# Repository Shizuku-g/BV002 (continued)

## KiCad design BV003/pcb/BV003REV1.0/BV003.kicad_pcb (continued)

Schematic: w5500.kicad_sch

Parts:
C132: 0.1uF; C_0402_1005Metric; PARTNO GRM155R61A475MEAAD
C140: 100nf; C_0402_1005Metric; PARTNO GRM188R61E106KA73D
C145, C215: 10uF; C_0603_1608Metric; PARTNO CL10A106MO8NQNC; LCSC C92487 Hot
C206, C209, C210, C211, C212, C213: 0.1uF; C_0603_1608Metric; PARTNO CL10A106MO8NQNC; LCSC C92487 Hot
C207, C214, C216, C217: 10nf; C_0402_1005Metric; PARTNO GRM188R61E106KA73D
C208: 4.7uF; C_0402_1005Metric; PARTNO GRM155R61A475MEAAD
C218: 22nf; C_0402_1005Metric; PARTNO GRM188R61E106KA73D
FB9: D_0201_0603Metric
J7: RJ45_Hanrun_HR911105A_Horizontal
MISO1: TestPoint_Pad_D1.5mm
MOSI1: TestPoint_Pad_D1.5mm
R4: 1k; R_0402_1005Metric; PARTNO RC0402FR-071KL; LCSC C106235
R14: 10k; R_0402_1005Metric; PARTNO RC0402FR-071KL; LCSC C106235
R31: 10k; R_0402_1005Metric; PARTNO RC0402FR-072KL; LCSC C60488
R55: 12.4k; R_0402_1005Metric; PARTNO RC0402FR-072KL; LCSC C60488
R73, R104, R105, R126: 0R; R_0402_1005Metric; PARTNO RC0402FR-071KL; LCSC C106235
R127, R128, R129, R130: 49R9; R_0402_1005Metric; PARTNO RC0402FR-071KL; LCSC C106235
R131: 10R; R_0402_1005Metric; PARTNO RC0402FR-071KL; LCSC C106235
R132, R133: 0.33k; R_0402_1005Metric; PARTNO RC0402FR-071KL; LCSC C106235
RD+1: TestPoint_Pad_D1.5mm
RD-1: TestPoint_Pad_D1.5mm
SCLK1: TestPoint_Pad_D1.5mm
SCSN1: TestPoint_Pad_D1.5mm
TXN1: TestPoint_Pad_D1.5mm
TXP1: TestPoint_Pad_D1.5mm
U32: 25MHz; Oscillator_SMD_EuroQuartz_XO32-4Pin_3.2x2.5mm; PARTNO SX3M25.000E20F30THN
U33: W5500; LQFP-48_7x7mm_P0.5mm

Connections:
1V2_1: C207.2, U33.22 (1V2O); also elsewhere on the board
+3V3: C140.2, C145.1, FB9.2, J7.9, J7.12, R14.1, R31.2, R128.1, R129.1, R131.1, U32.1 (Standby), U32.4 (VDD); also elsewhere on the board
/T-Display-S3/MISO: MISO1.1, U33.34 (MISO); also elsewhere on the board
/T-Display-S3/MOSI: MOSI1.1, U33.35 (MOSI); also elsewhere on the board
/T-Display-S3/SCLK: SCLK1.1, U33.33 (SCLK); also elsewhere on the board
/T-Display-S3/SCSN: SCSN1.1, U33.32 (~SCS); also elsewhere on the board
/T-Display-S3/w5500/ACTLED: R133.2, U33.27 (ACTLED)
/T-Display-S3/w5500/LINKLED: R132.2, U33.25 (LINKLED)
AVDD: C206.1, C209.1, C210.1, C211.1, C212.1, C213.1, C215.1, FB9.1, U33.4 (AVDD), U33.8 (AVDD), U33.11 (AVDD), U33.15 (AVDD), U33.17 (AVDD), U33.21 (AVDD)
GND: C132.1, C206.2, C207.1, C208.1, C209.2, C210.2, C211.2, C212.2, C213.2, C214.1, C215.2, C218.1, J7.SH, R55.1, U32.2 (GND), U33.3 (AGND), U33.9 (AGND), U33.14 (AGND), U33.16 (AGND), U33.19 (AGND), U33.29 (GND), U33.43 (PMODE2), U33.44 (PMODE1), U33.45 (PMODE0), U33.48 (AGND); also elsewhere on the board
unnamed: C132.2, R4.1, R14.2
unnamed: C216.2, R126.2, R127.1
unnamed: C217.2, R105.2, R130.1
unnamed: J7.10, R133.1
unnamed: J7.11, R132.1
unnamed: C214.2, J7.5 (RCT), R127.2, R130.2
unnamed: C216.1, J7.3 (RD+), RD+1.1 (1_1)
unnamed: C217.1, J7.6 (RD-), RD-1.1 (1_1)
unnamed: C218.2, J7.4 (TCT), R131.2
unnamed: J7.1 (TD+), R104.2, R129.2, TXP1.1 (1_1)
unnamed: J7.2 (TD-), R73.2, R128.2, TXN1.1 (1_1)
unnamed: U32.3 (Out), U33.30 (XI/CLKIN)
unnamed: R55.2, U33.10 (EXRES1)
unnamed: R105.1, U33.5 (RXN)
unnamed: R126.1, U33.6 (RXP)
unnamed: C208.2, U33.20 (TOCAP)
unnamed: R73.1, U33.1 (TXN)
unnamed: R104.1, U33.2 (TXP)
unnamed: C140.1, C145.2, U33.28 (VDD)
unnamed: R31.1, U33.36 (~INT)
unnamed: R4.2, U33.37 (~RST)

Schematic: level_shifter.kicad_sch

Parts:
C98: 0.1uF; C_0402_1005Metric; PARTNO KGM05AR71C104KH
C99: 1uF; C_0402_1005Metric; PARTNO EMK105BJ105MV-F
R19, R22, R25, R28, R32, R33, R34, R35, R36: 1k; R_0402_1005Metric; PARTNO RC0402FR-071KL
R20, R21, R23, R24, R26, R27, R29, R30: 10k; R_0402_1005Metric; PARTNO RC0402JR-0710KL
U18: TLV3544; TSSOP-14_4.4x5mm_P0.65mm; PARTNO TLV3544IPWR

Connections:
+5V: C98.2, C99.2, U18.4 (V+); also elsewhere on the board
/BM1370/bm1373_3/BO: R27.1; also elsewhere on the board
/BM1370/bm1373_3/CO: R21.1; also elsewhere on the board
/BM1370/bm1373_3/RI: R36.1; also elsewhere on the board
/BM1370/bm1373_3/RSTO: R24.1; also elsewhere on the board
/BM1370/bm1373_4/level_shifter/BI2: R34.1, U18.8; also elsewhere on the board
/BM1370/bm1373_4/level_shifter/CI2: R32.1, U18.1; also elsewhere on the board
/BM1370/bm1373_4/level_shifter/NRSTI2: R33.1, U18.7; also elsewhere on the board
/BM1370/bm1373_4/level_shifter/RO2: R30.1; also elsewhere on the board
unnamed: R35.1, R36.2, U18.14
unnamed: R20.1, R21.2, U18.3 (+)
unnamed: R19.1, R32.2, U18.2 (-)
unnamed: R23.2, R24.2, U18.5 (+)
unnamed: R22.1, R33.2, U18.6 (-)
unnamed: R26.2, R27.2, U18.10 (+)
unnamed: R25.1, R34.2, U18.9 (-)
unnamed: R29.2, R30.2, U18.12 (+)
unnamed: R28.1, R35.2, U18.13 (-)
VDD: R20.2, R23.1, R26.1; also elsewhere on the board
VDD2: C98.1, C99.1, R29.1, U18.11 (V-); also elsewhere on the board
VDD3: R19.2, R22.2, R25.2, R28.2; also elsewhere on the board

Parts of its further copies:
C107, C109: 0.1uF; C_0402_1005Metric; PARTNO KGM05AR71C104KH
C108, C110: 1uF; C_0402_1005Metric; PARTNO EMK105BJ105MV-F
R43, R46, R49, R52, R56, R57, R58, R59, R60, R61, R64, R67, R70, R74, R75, R76, R77, R78: 1k; R_0402_1005Metric; PARTNO RC0402FR-071KL
R44, R45, R47, R48, R50, R51, R53, R54, R62, R63, R65, R66, R68, R69, R71, R72: 10k; R_0402_1005Metric; PARTNO RC0402JR-0710KL
U25, U26: TLV3544; TSSOP-14_4.4x5mm_P0.65mm; PARTNO TLV3544IPWR

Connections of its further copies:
+5V: C107.2, C108.2, C109.2, C110.2, U25.4 (V+), U26.4 (V+); also elsewhere on the board
/BM1370/bm1373_1/BO: R51.1; also elsewhere on the board
/BM1370/bm1373_1/CO: R45.1; also elsewhere on the board
/BM1370/bm1373_1/RI: R60.1; also elsewhere on the board
/BM1370/bm1373_1/RSTO: R48.1; also elsewhere on the board
/BM1370/bm1373_2/BO: R69.1; also elsewhere on the board
/BM1370/bm1373_2/CO: R63.1; also elsewhere on the board
/BM1370/bm1373_2/RI: R78.1; also elsewhere on the board
/BM1370/bm1373_2/RSTO: R66.1; also elsewhere on the board
/BM1370/bm1373_2/level_shifter/BI2: R58.1, U25.8; also elsewhere on the board
/BM1370/bm1373_2/level_shifter/CI2: R56.1, U25.1; also elsewhere on the board
/BM1370/bm1373_2/level_shifter/NRSTI2: R57.1, U25.7; also elsewhere on the board
/BM1370/bm1373_2/level_shifter/RO2: R54.1; also elsewhere on the board
/BM1370/bm1373_3/level_shifter/BI2: R76.1, U26.8; also elsewhere on the board
/BM1370/bm1373_3/level_shifter/CI2: R74.1, U26.1; also elsewhere on the board
/BM1370/bm1373_3/level_shifter/NRSTI2: R75.1, U26.7; also elsewhere on the board
/BM1370/bm1373_3/level_shifter/RO2: R72.1; also elsewhere on the board
GND: C107.1, C108.1, R53.1, U25.11 (V-); also elsewhere on the board
unnamed: R59.1, R60.2, U25.14
unnamed: R77.1, R78.2, U26.14
unnamed: R44.1, R45.2, U25.3 (+)
unnamed: R43.1, R56.2, U25.2 (-)
unnamed: R47.2, R48.2, U25.5 (+)
unnamed: R46.1, R57.2, U25.6 (-)
unnamed: R50.2, R51.2, U25.10 (+)
unnamed: R49.1, R58.2, U25.9 (-)
unnamed: R53.2, R54.2, U25.12 (+)
unnamed: R52.1, R59.2, U25.13 (-)
unnamed: R62.1, R63.2, U26.3 (+)
unnamed: R61.1, R74.2, U26.2 (-)
unnamed: R65.2, R66.2, U26.5 (+)
unnamed: R64.1, R75.2, U26.6 (-)
unnamed: R68.2, R69.2, U26.10 (+)
unnamed: R67.1, R76.2, U26.9 (-)
unnamed: R71.2, R72.2, U26.12 (+)
unnamed: R70.1, R77.2, U26.13 (-)
VDD1: C109.1, C110.1, R43.2, R46.2, R49.2, R52.2, R71.1, U26.11 (V-); also elsewhere on the board
VDD2: R44.2, R47.1, R50.1, R61.2, R64.2, R67.2, R70.2; also elsewhere on the board
VDD3: R62.2, R65.1, R68.1; also elsewhere on the board

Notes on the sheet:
OPAMP Bypass

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
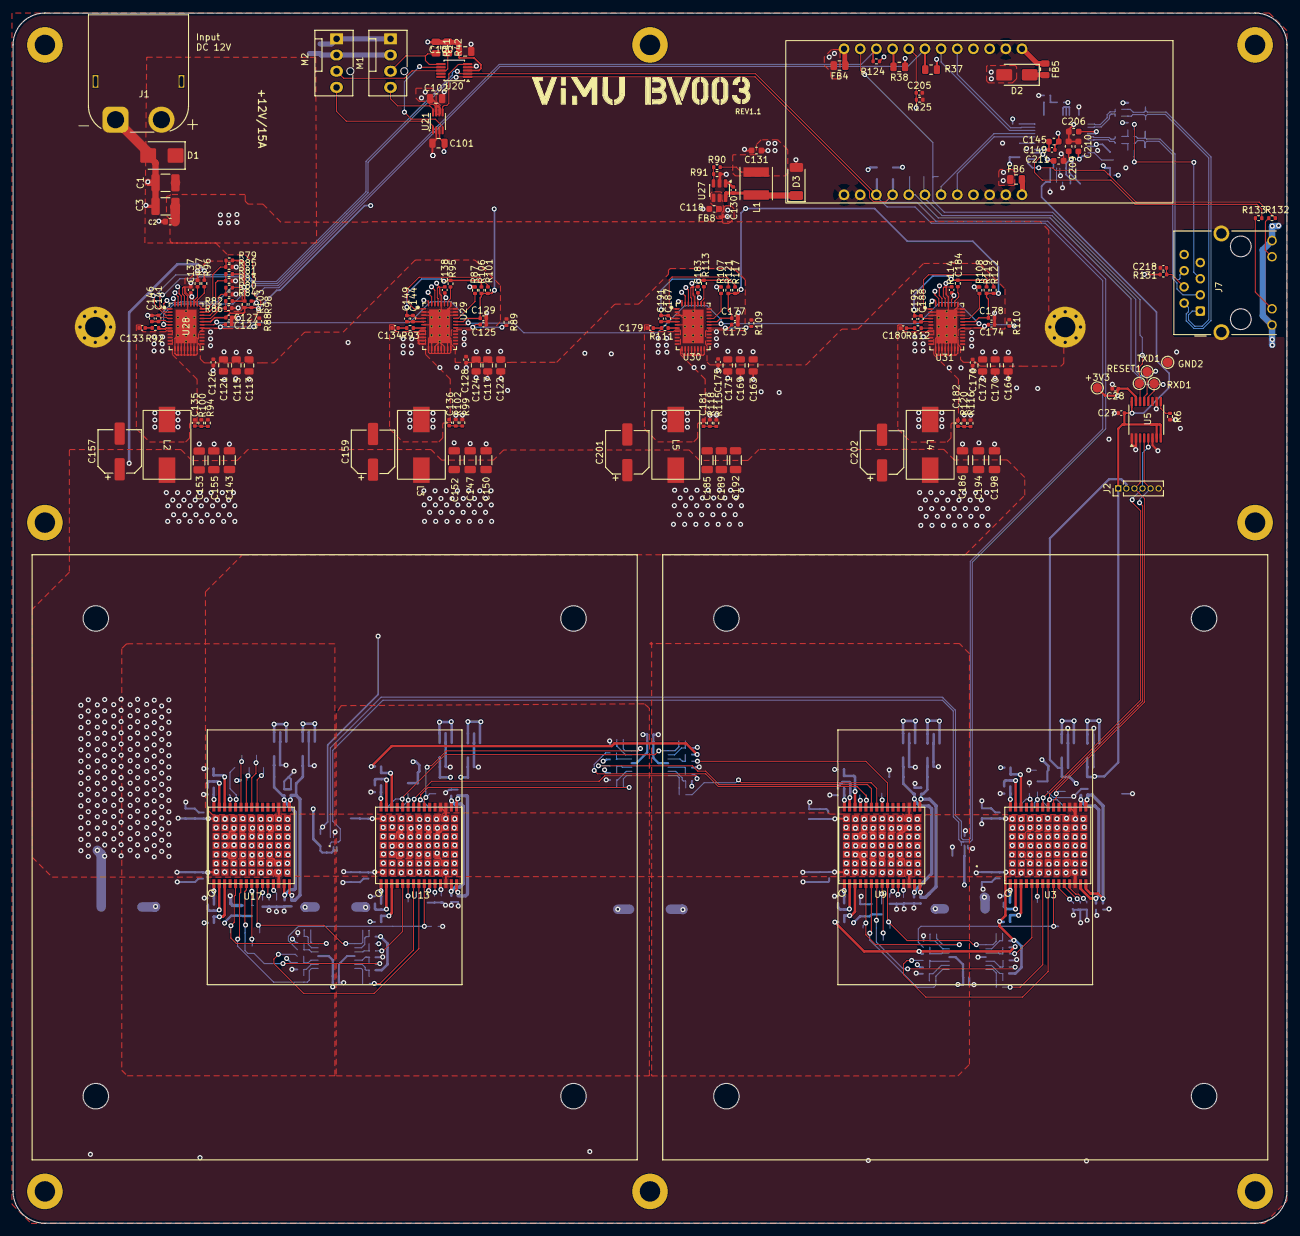
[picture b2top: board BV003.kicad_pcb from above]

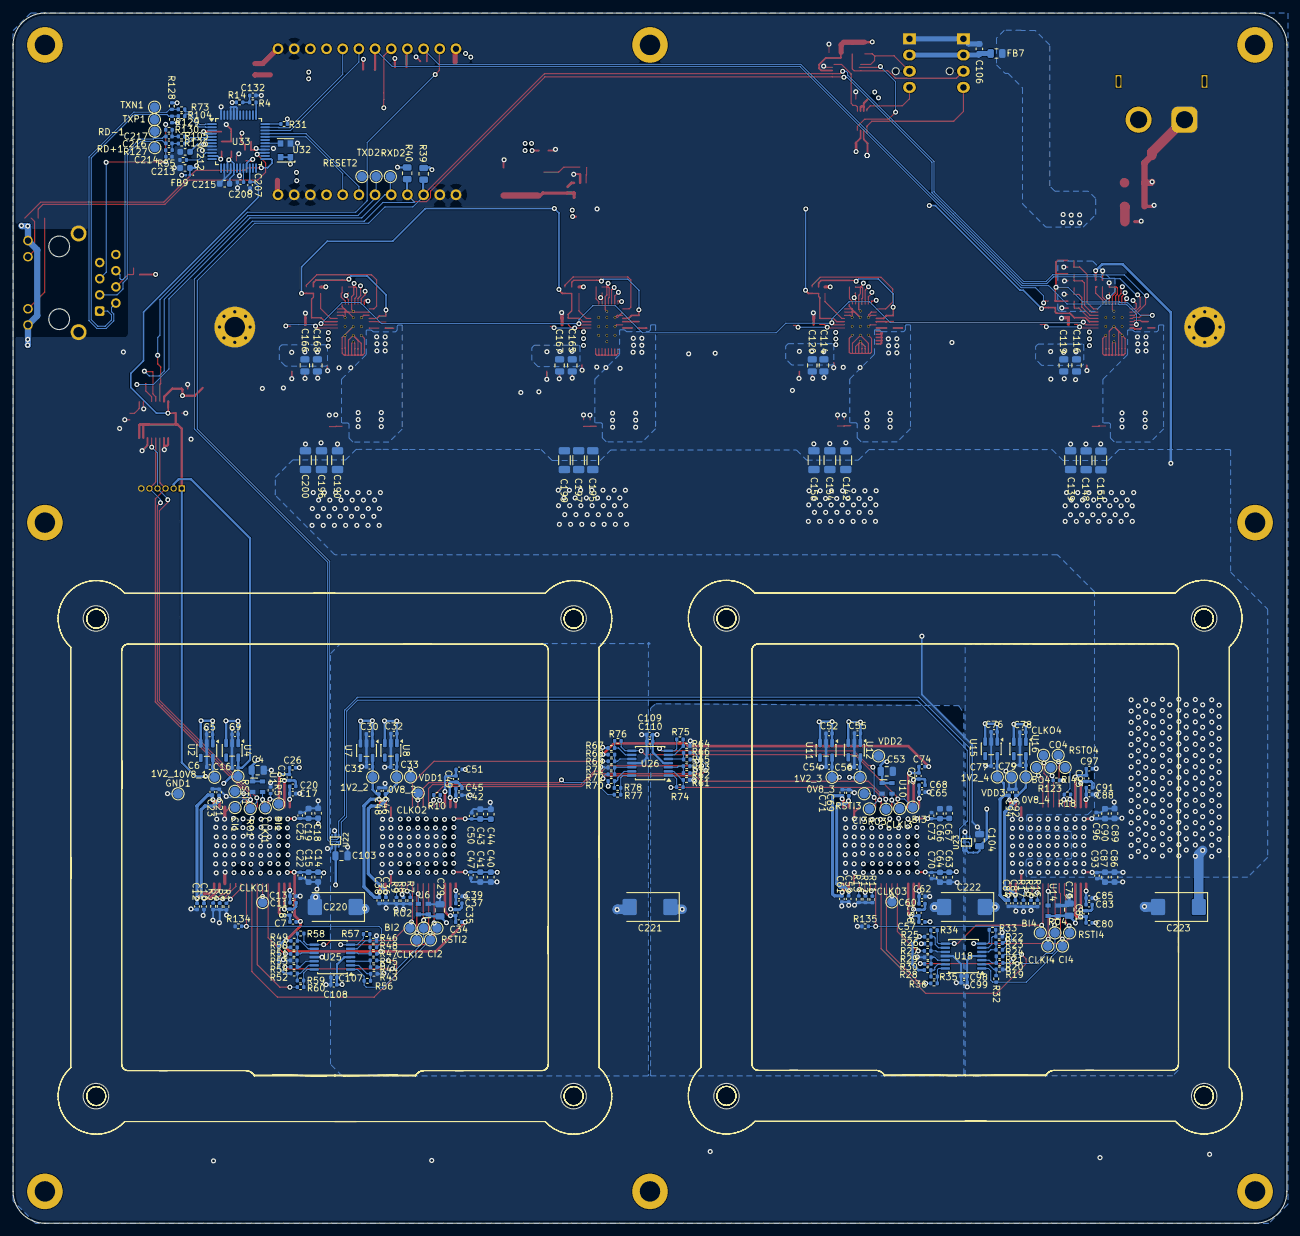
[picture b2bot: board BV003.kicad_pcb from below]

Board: 4 copper layers, 200.0 x 190.0 mm, 457 parts (285 on the bottom side), 224 nets.

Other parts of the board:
C220, C221, C222, C223: 330uf; CP_EIA-7343-31_Kemet-D_Pad2.25x2.55mm_HandSolder
CLKO1, CLKO2, CLKO3: TestPoint_Pad_D1.5mm
GND2: TestPoint_Pad_D1.5mm
H1, H2: MountingHole_Pad; MountingHole_3.2mm_M3_Pad_Via
R134, R135: 10k; R_0402_1005Metric

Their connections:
/BM1370/bm1373_1/RSTO: R134.2; also elsewhere on the board
/BM1370/bm1373_3/RSTO: R135.2; also elsewhere on the board
GND: C220.2, GND2.1 (1_1), H1.1 (1_1), H2.1 (1_1), R134.1; also elsewhere on the board
unnamed 110: CLKO1.1 (1_1); also elsewhere on the board
unnamed 121: CLKO2.1 (1_1); also elsewhere on the board
unnamed 131: CLKO3.1 (1_1); also elsewhere on the board
VDD: C223.1; also elsewhere on the board
VDD1: C220.1, C221.2; also elsewhere on the board
VDD2: C221.1, C222.2, R135.1; also elsewhere on the board
VDD3: C222.1, C223.2; also elsewhere on the board

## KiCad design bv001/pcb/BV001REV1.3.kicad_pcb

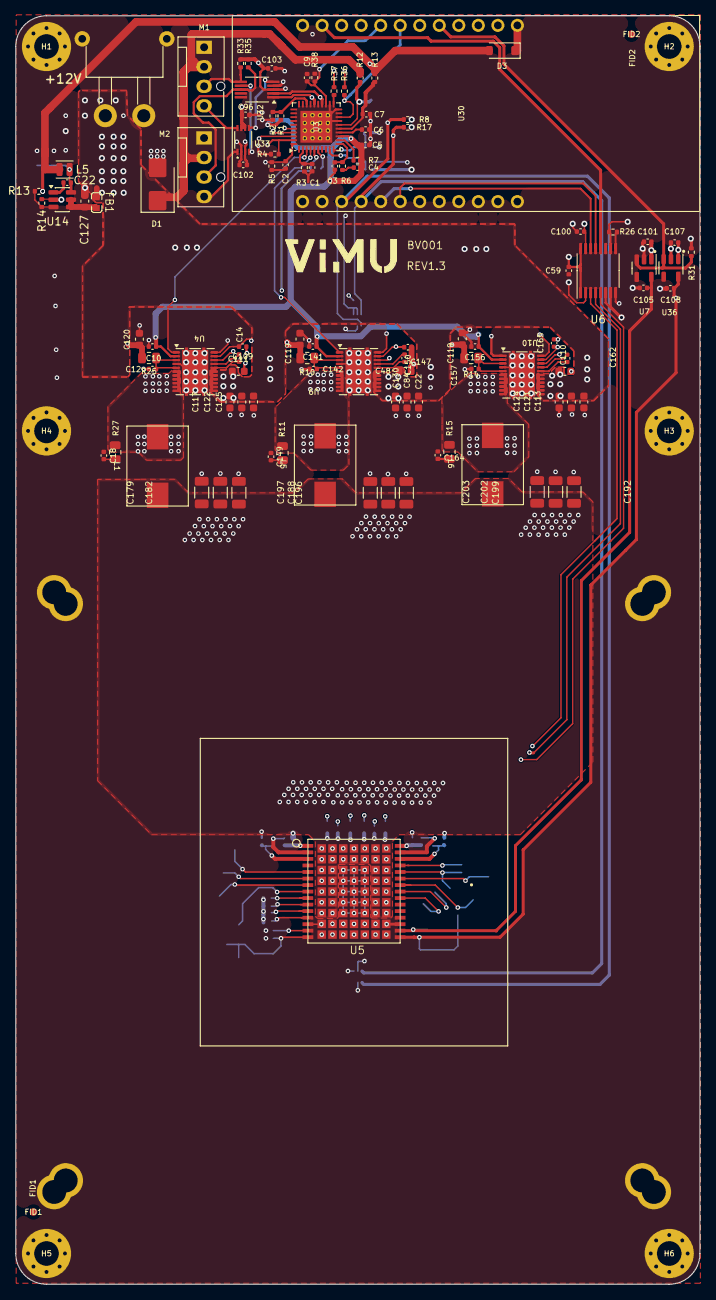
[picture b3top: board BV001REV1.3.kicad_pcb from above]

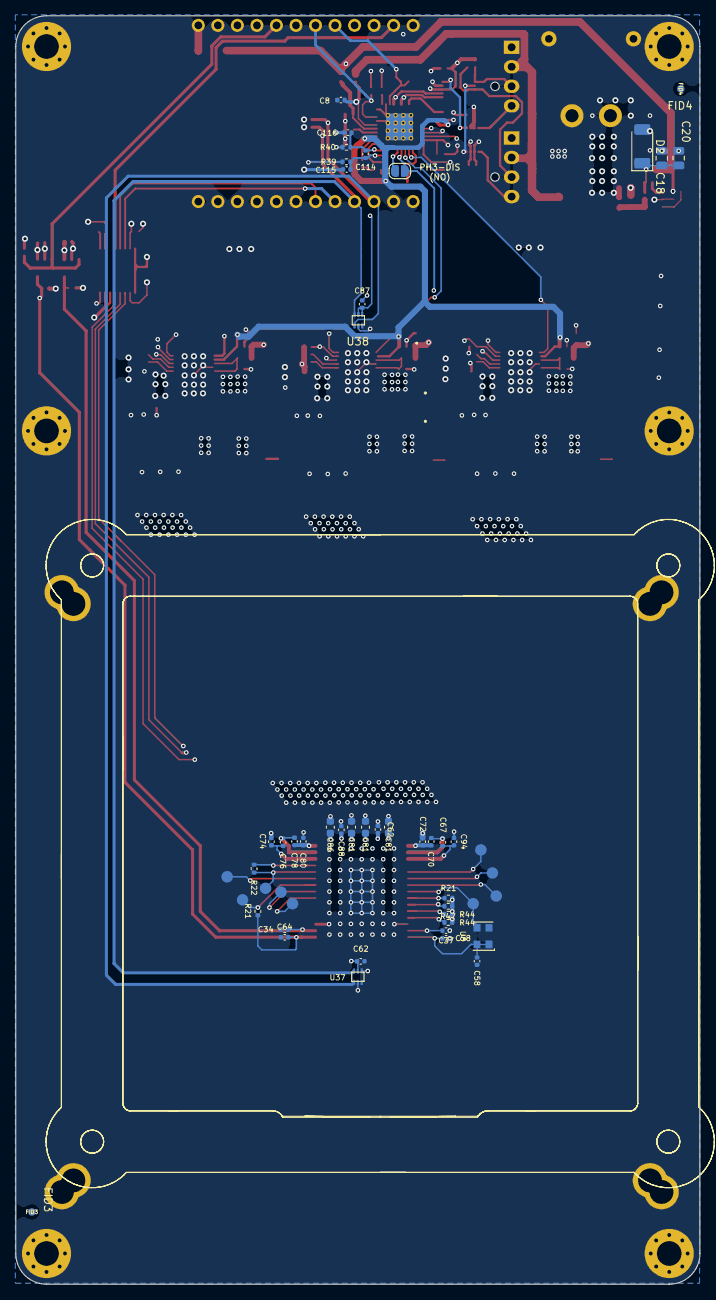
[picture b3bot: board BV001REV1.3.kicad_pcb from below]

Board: 6 copper layers, 89.0 x 165.0 mm, 156 parts (42 on the bottom side), 79 nets.

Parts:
C1: 2.2nF; C_0402_1005Metric
C2, C4, C9, C18, C109, C149, C150, C164, C165: 1nF; C_0402_1005Metric
C3: 12pF; C_0402_1005Metric
C5: 330nF; C_0402_1005Metric
C6, C8, C34, C37, C58, C58#2, C64, C67, C70, C72, C74, C76, C78, C80, C94, C105, C108: 1µF; C_0402_1005Metric
C7: 4.7µF; C_0402_1005Metric
C10, C14, C87, C96, C101, C102, C103, C107, C141, C147, C156, C162: 100nF; C_0402_1005Metric
C12, C142, C157: 2.2µF; C_0402_1005Metric
C18#2, C20: 10uF; C_0805_2012Metric
C22, C48, C81, C81#2, C81#3, C84, C86, C110, C111, C113, C117, C121, C122, C124, C125, C127, C130: 10uF; C_0603_1608Metric
C22#2: 10nf; C_0402_1005Metric
C59, C100: 0.1uF; C_0402_1005Metric
C62: 100pF; C_0402_1005Metric
C62#2: 100nf; C_0402_1005Metric
C88: 33pf; C_0402_1005Metric
C114, C115, C116: 22pF; C_0402_1005Metric
C119, C119#2, C120: 10µF; C_0603_1608Metric
C179, C182, C188, C192, C196, C197, C199, C202, C203: 100µF; C_1206_3216Metric
D1: 5KPxxA; D_SMB
D2: D_SOD-128
D3: 1N5819; D_SOD-123
FB1: FB0603
FID1, FID2, FID3, FID4: Fiducial_1mm_Mask2mm
H1, H2, H3, H4, H5, H6: MountingHole_Pad; MountingHole_3.2mm_M3_Pad_Via
J1: XT30; XT30PW-M
JP3: SolderJumper_2_Open; SolderJumper-2_P1.3mm_Open_RoundedPad1.0x1.5mm
L1, L5#2, L6: 220nH; IFLR-4031GC-01-8x10
L5: 4.7uH; L_Changjiang_FTC201612S
M1, M2: Fan_4pin; FanPinHeader_1x04_P2.54mm_Vertical
R1: 16.5k; R_0402_1005Metric
R2: 24.3k; R_0402_1005Metric
R3: 66.5k; R_0402_1005Metric
R4: 100k; R_0402_1005Metric
R5: 121k; R_0402_1005Metric
R6: 8.06k; R_0402_1005Metric
R7: 2.55k; R_0402_1005Metric
R8, R17: 4.7k; R_0402_1005Metric
R10, R11, R14, R15, R25, R27: 1R/0.5w; R_0805_2012Metric
R12, R13: 2.2R; R_0402_1005Metric
R13#2: 84.5k; R_0402_1005Metric
R14#2: 16.2k; R_0402_1005Metric
R21, R21#2, R22, R31, R36, R37, R38: 10k; R_0402_1005Metric
R26: 20k; R_0402_1005Metric
R33, R35: 2.7k; R_0402_1005Metric
R39, R40: 100R; R_0402_1005Metric
R44, R44#2, R47: 1k; R_0402_1005Metric
U3: TPS53647; Texas_RHA0040B_VQFN-40-1EP_6x6mm_P0.5mm_EP4.15x4.15mm_Therm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
U4, U9, U10: CSD95472Q5MC; CSD95472-SON-5x6
U5: B1373CC
U6: SN74AVC4T774; TSSOP-16_4.4x5mm_P0.65mm
U7: MCP1824T-0802E; SOT-23-5
U8: 25MHz; Oscillator_SMD_EuroQuartz_XO32-4Pin_3.2x2.5mm
U14: SOT-23-6
U30: T-Display-S3
U32: EMC2302-1; MSOP-10_3x3mm_P0.5mm
U33: TXU0102-DCU; VSSOP-8_2.3x2mm_P0.5mm
U36: MCP1824T-1202E; SOT-23-5
U37, U38: TMP1075; TMP1075-DRL

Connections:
+0V8: C34.2, C37.2, C105.1, U5.14 (VDDIO_08_0), U5.17 (VDDIO_08_1), U7.5 (VOUT)
+1V2: C58.1, C58#2.1, C59.1, C64.1, C108.1, R21.2, U5.15 (VDDIO_12_0), U5.16 (VDDIO_12_1), U6.1 (DIR1), U6.8 (DIR4), U6.16 (VCCA), U8.1 (Standby), U8.4 (VDD), U36.5 (VOUT)
+3V3: C62#2.2, C87.1, C100.1, C101.1, C102.1, C103.1, C107.1, JP3.2 (B), R8.2, R17.2, R33.1, R35.1, R36.1, R37.1, U3.6 (CSP4), U6.15 (VCCB), U7.1 (VIN), U30.1 (3V), U30.13 (3V), U32.3 (VDD), U33.3 (VCCA), U36.1 (VIN), U37.5 (V+), U38.4 (A0), U38.5 (V+)
+5V: C96.1, C119.1, C119#2.1, C120.1, D3.2 (A), L5.2, R10.1, R13.1, R13#2.2, R14.1, R25.1, U33.6 (OE), U33.7 (VCCB)
+12V: C22.1, C48.1, C84.1, C110.1, C111.1, C113.1, C117.1, C121.1, C122.1, C124.1, C125.1, C130.1, D1.1 (A1), FB1.1, J1.1 (+V), M1.2 (+), M2.2 (+), R12.1, U4.7 (VIN), U9.7 (VIN), U10.7 (VIN)
+VRef: C3.2, C4.2, C5.1, C10.1, C141.1, C156.1, R1.2, R7.1, U3.13 (VREF), U4.2 (REFIN), U9.2 (REFIN), U10.2 (REFIN)
/BM1366/BI: R21#2.2, U5.9 (BI)
/BM1366/RESET: U6.12 (B3), U30.2 (GPIO1)
/BM1366/RXD: U6.14 (B1), U30.20 (GPIO18)
/BM1366/TXD: U6.13 (B2), U30.19 (GPIO17)
/Power/FCCM: R4.2, U3.39 (/SKIP-NVM), U4.10 (FCCM), U9.10 (FCCM), U10.10 (FCCM)
/Power/LDO_EN: R31.1, U7.3 (EN), U30.8 (GPIO13), U36.3 (EN)
/Power/PWR_EN: C9.1, R38.1, U3.23 (ENABLE), U30.5 (GPIO10)
/Power/TPS_CSP1: U3.3 (CSP1), U4.1 (IOUT)
/Power/TPS_CSP2: U3.4 (CSP2), U9.1 (IOUT)
/Power/TPS_CSP3: JP3.1 (A), U3.5 (CSP3), U10.1 (IOUT)
/Power/TPS_PWM1: U3.38 (PWM1), U4.12 (PWM)
/Power/TPS_PWM2: U3.37 (PMW2), U9.12 (PWM)
/Power/TPS_PWM3: U3.36 (PMW3), U10.12 (PWM)
/Power/TPS_TSEN: C2.1, C109.1, C150.1, C165.1, R5.2, U3.40 (TSEN), U4.11 (TAO/FAULT), U9.11 (TAO/FAULT), U10.11 (TAO/FAULT)
/Power/VR_RDY: R36.2, U3.18 (VR_RDY), U30.6 (GPIO11)
/Power//RESET: R37.2, U3.21 (/RESET)
/T-Display-S3/SCL: R8.1, U3.24 (PMB_CLK), U30.22 (GPIO43), U32.2 (SCL), U37.1 (SCL), U38.1 (SCL)
/T-Display-S3/SDA: R17.1, U3.26 (PMB_DIO), U30.21 (GPIO44), U32.1 (SDA), U37.6 (SDA), U38.6 (SDA)
/T-Display-S3/TACHO1: M1.3 (Tacho), R33.2, U32.6 (TACH1)
/T-Display-S3/TACHO2: M2.3 (Tacho), R35.2, U32.8 (TACH2)
CI-N: U5.6 (CI), U6.4 (A2)
CLK-N: U5.8 (CLKI), U8.3 (Out)
GND: C1.2, C2.2, C5.2, C6.2, C7.1, C8.1, C9.2, C10.2, C12.2, C18.2, C18#2.2, C20.2, C22.2, C34.1, C37.1, C48.2, C58.2, C58#2.2, C59.2, C62.2, C62#2.1, C64.2, C72.2, C80.2, C81.2, C81#2.2, C81#3.2, C84.2, C86.2, C87.2, C88.2, C96.2, C100.2, C101.2, C102.2, C103.2, C105.2, C107.2, C108.2, C109.2, C110.2, C111.2, C113.2, C115.1, C116.2, C117.2, C119.2, C119#2.2, C120.2, C121.2, C122.2, C124.2, C125.2, C127.2, C130.2, C141.2, C142.2, C149.2, C150.2, C156.2, C157.2, C164.2, C165.2, C179.2, C182.2, C188.2, C192.2, C196.2, C197.2, C199.2, C202.2, C203.2, D1.2 (A2), D2.2, H1.1, H2.1, H3.1, H4.1, H5.1, H6.1, J1.2 (GND), M1.1 (-), M2.1 (-), R2.1, R3.1, R4.1, R5.1, R14#2.1, R21#2.1, R26.1, R31.2, R38.2, R40.1, R44.2, R44#2.2, R47.2, U3.17 (GND), U3.20 (GND), U3.22 (GND), U3.41 (EP), U4.4 (PGND), U4.13 (PGND), U5.13 (GND), U5.18 (GND), U5.32 (VDD1), U6.2 (DIR2), U6.6 (A4), U6.7 (DIR3), U6.10 (GND), U7.2 (GND), U8.2 (GND), U9.4 (PGND), U9.13 (PGND), U10.4 (PGND), U10.13 (PGND), U14.2 (GND), U30.11 (GND), U30.14 (GND), U30.15 (GND), U30.23 (GND), U30.24 (GND), U32.4 (GND), U33.2 (GND), U36.2 (GND), U37.2 (GND), U37.4 (A0), U38.2 (GND)
MODE1: R47.1, U5.10 (LITE_PAD)
MODE2: R44#2.1, U5.11 (PIN_MODE)
MODE3: R44.1, U5.12 (NC)
unnamed: C4.1, R6.1
unnamed: C18.1, R27.1
unnamed: C149.1, R11.1
unnamed: C164.1, R15.1
unnamed: D3.1 (K), U30.12 (5V)
unnamed: M1.4 (PWM), U33.8 (B1Y)
unnamed: M2.4 (PWM), U33.1 (B2Y)
unnamed: R1.1, R2.2, U3.28 (ADDR_TRISE)
unnamed: C3.1, R6.2, U3.11 (COMP)
unnamed: C1.1, R3.2, U3.2 (IMON)
unnamed: R7.2, U3.12 (ISUM)
unnamed: C6.1, U3.14 (V3R3)
unnamed: C7.2, R13.2, U3.15 (V5)
unnamed: C8.2, R12.2, U3.16 (VIN)
unnamed: C114.2, C116.1, R40.2, U3.10 (VSN)
unnamed: C114.1, C115.2, R39.2, U3.9 (VSP)
unnamed: C14.1, U4.9 (BOOT)
unnamed: C14.2, U4.8 (BOOT_R)
unnamed: C12.1, R25.2, U4.3 (ENABLE), U4.5 (VDD)
unnamed: L1.1, R27.2, U4.6 (VSW)
unnamed: R26.2, U6.9 (OE)
unnamed: C147.1, U9.9 (BOOT)
unnamed: C147.2, U9.8 (BOOT_R)
unnamed: C142.1, R10.2, U9.3 (ENABLE), U9.5 (VDD)
unnamed: L5#2.1, R11.2, U9.6 (VSW)
unnamed: C162.1, U10.9 (BOOT)
unnamed: C162.2, U10.8 (BOOT_R)
unnamed: C157.1, R14.2, U10.3 (ENABLE), U10.5 (VDD)
unnamed: L6.1, R15.2, U10.6 (VSW)
unnamed: C22#2.2, U14.1 (BS)
unnamed: C127.1, FB1.2, U14.4 (EN), U14.5 (IN)
unnamed: R13#2.1, R14#2.2, U14.3 (FB)
unnamed: C18#2.1, C20.1, C22#2.1, D2.1, L5.1, U14.6 (SW)
unnamed: U32.5 (PWM1), U33.5 (A1)
unnamed: U32.7 (PWM2), U33.4 (A2)
RI-1.2: R21.1, U5.24 (RI)
RO-N: U5.7 (RO), U6.3 (A1)
RST-0: R22.2, U5.26 (RST)
RST-N: U5.5 (RSTI), U6.5 (A3)
VDD: C62.1, C74.1, C81.1, C81#2.1, C81#3.1, C86.1, C88.1, C94.2, C179.1, C182.1, C188.1, C192.1, C196.1, C197.1, C199.1, C202.1, C203.1, L1.2, L5#2.2, L6.2, R39.1, U5.31 (VDD)
VDD1_0: C70.2, C72.1, U5.1 (VDD1_0)
VDD1_1: C78.1, C80.1, U5.30 (VDD1_1)
VDD2_0: C67.2, C70.1, U5.2 (VDD2_0)
VDD2_1: C76.2, C78.2, U5.29 (VDD2_1)
VDD3_0: C67.1, C94.1, U5.3 (VDD3_0)
VDD3_1: C74.2, C76.1, U5.28 (VDD3_1)
VSS: R22.1, U5.27 (VSS)
